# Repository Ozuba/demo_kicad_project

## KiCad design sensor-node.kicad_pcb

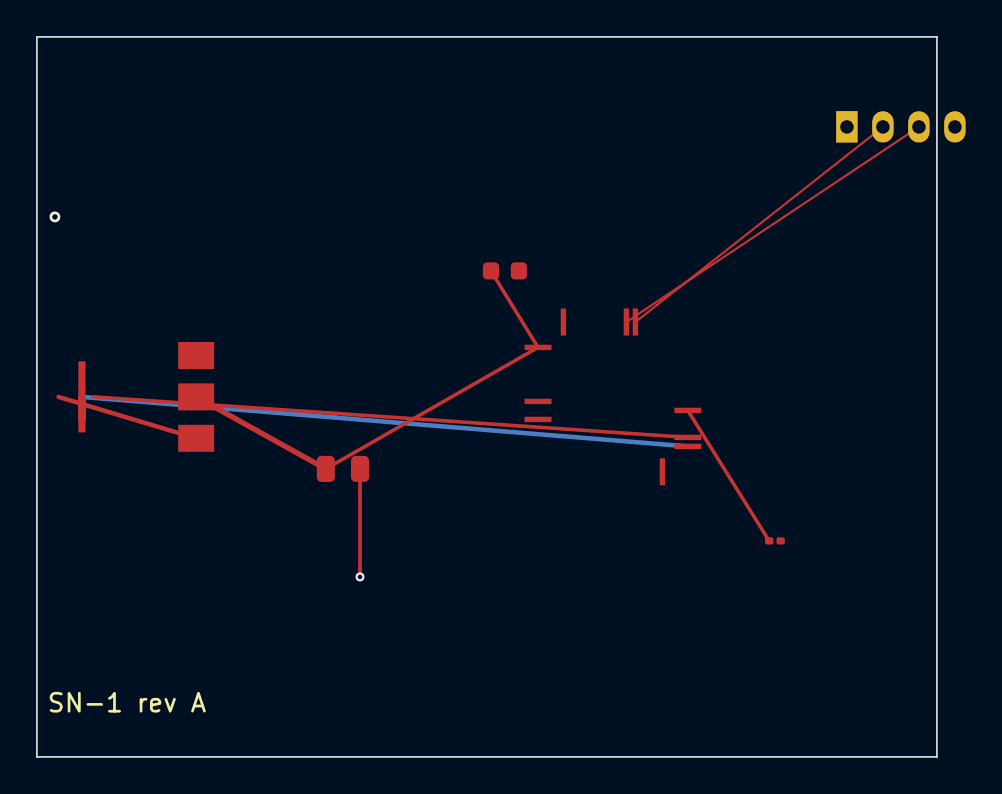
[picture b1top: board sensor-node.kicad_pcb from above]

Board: 2 copper layers, 50.0 x 40.0 mm, 7 parts (0 on the bottom side), 7 nets.

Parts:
C1: 10uF; C_0805_2012Metric
C2: 100nF; C_0603_1608Metric
C3: 100nF Y5V; C_0201_0603Metric
J1: USB_B_Micro; USB_Micro-B_Molex-105017-0001
J2: I2C_SENSOR_PORT; JST_PH_B4B-PH-K_1x04_P2.00mm_Vertical
U1: AMS1117-3.3; SOT-223-3_TabPin2
U2: STM32F103C8T6; LQFP-48_7x7mm_P0.5mm

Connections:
+12V_IN: J1.1, U1.3
/USB_DM: J1.2, U2.32
/USB_DP: J1.3, U2.33
GND: C1.2, C2.2, C3.2, J1.5, J2.4, U1.1
VCC: C1.1, C2.1, C3.1, J2.1, U1.2, U2.1, U2.9, U2.24, U2.36, U2.48
i2c_scl: J2.2, U2.42
i2c_sda: J2.3, U2.43
